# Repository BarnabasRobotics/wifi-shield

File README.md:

#Barnabas Robotics Wi-Fi shield
WIFI Shield for Barnabas-Bot and Arduino Uno
#First Schematic and basic board layout
We have added the first version of the barnabas bot Wi-Fi shield. This is version 1.0 with 4 DC motors max, and the NodeMCU Wi-Fi development board. There is no routing yet.  
#NodeMCU
Some information on NodeMCU 1.0 found here: https://github.com/nodemcu/nodemcu-devkit-v1.0
We have an EAGLE library for NodeMCU if you need to use it. This was developed by NodeMCU and it is also on their NodeMCU devkit v1.0 repository.  
#V2 
Some minor edits, added a GPIO header, and fixed some bad wires. Vincent will continue on the board layout.

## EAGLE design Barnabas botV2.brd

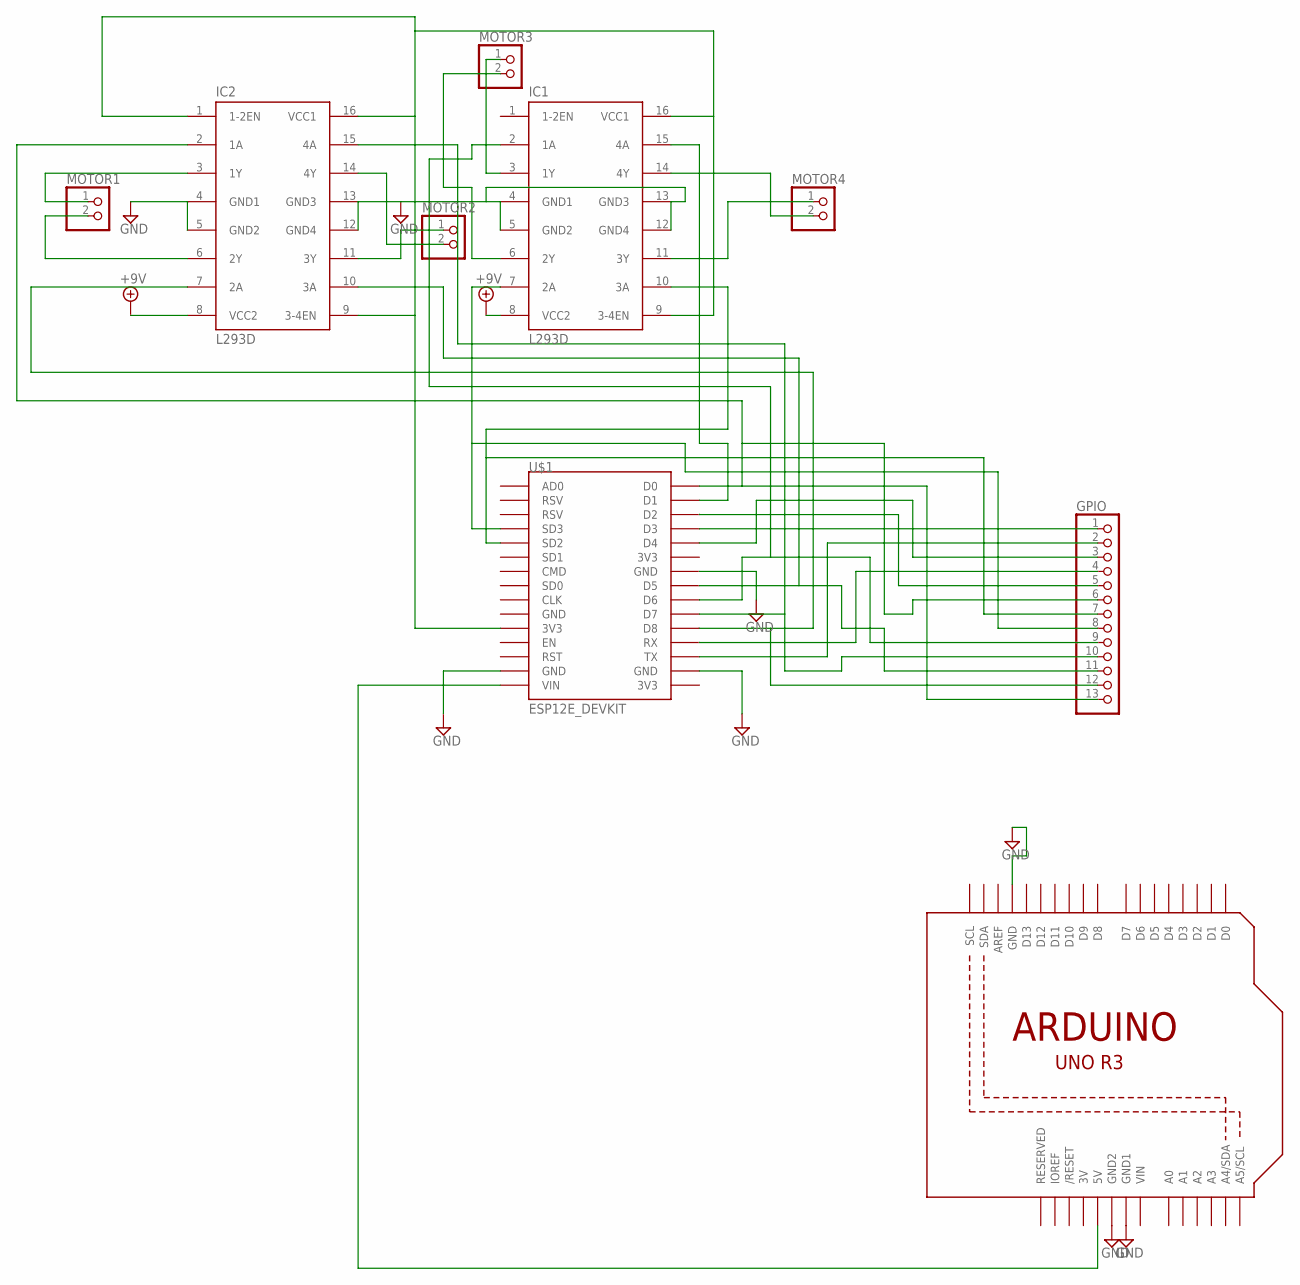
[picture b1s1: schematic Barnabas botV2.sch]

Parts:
GPIO: PINHD-1X13; 1X13
IC1, IC2: L293D; DIL16
MOTOR1, MOTOR2, MOTOR3, MOTOR4: PINHD-1X2; 1X02
U1: ARDUINOR3-DIMENSION; ARDUINOR3
U$1: ESP12E_DEVKIT

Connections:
3V: U1.3V
+9V: IC1.8 (VCC2), IC2.8 (VCC2)
GND: IC1.4 (GND1), IC1.5 (GND2), IC1.12 (GND4), IC1.13 (GND3), IC2.4 (GND1), IC2.5 (GND2), IC2.12 (GND4), IC2.13 (GND3), U1.GND, U1.GND1, U1.GND2, U$1.GND@1 (GND), U$1.GND@2 (GND), U$1.GND@3 (GND)
unnamed: GPIO.1, U$1.D3
unnamed: GPIO.12, IC2.7 (2A), U$1.D8
unnamed: IC1.9 (3-4EN), IC1.16 (VCC1), IC2.1 (1-2EN), IC2.9 (3-4EN), IC2.16 (VCC1), U$1.3V3@0 (3V3)
unnamed: GPIO.11, IC2.10 (3A), U$1.D5
unnamed: GPIO.10, IC2.15 (4A), U$1.D7
unnamed: GPIO.9, IC1.2 (1A), U$1.D6
unnamed: GPIO.8, IC1.7 (2A), U$1.SD3
unnamed: GPIO.7, IC1.10 (3A), U$1.SD2
unnamed: IC1.15 (4A), U$1.D1
unnamed: IC2.3 (1Y), MOTOR1.1
unnamed: IC2.6 (2Y), MOTOR1.2
unnamed: IC2.11 (3Y), MOTOR2.1
unnamed: IC2.14 (4Y), MOTOR2.2
unnamed: IC1.3 (1Y), MOTOR3.1
unnamed: IC1.14 (4Y), MOTOR4.2
unnamed: IC1.11 (3Y), MOTOR4.1
unnamed: GPIO.2, U$1.TX
unnamed: U1.5V, U$1.VIN
unnamed: GPIO.3, U$1.D4
unnamed: GPIO.4, U$1.RX
unnamed: GPIO.5, U$1.D2
unnamed: GPIO.6, GPIO.13, IC2.2 (1A), U$1.D0
VIN: U1.VIN

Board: 2 copper layers, 9 parts (0 on the bottom side), 24 nets, no tracks yet.

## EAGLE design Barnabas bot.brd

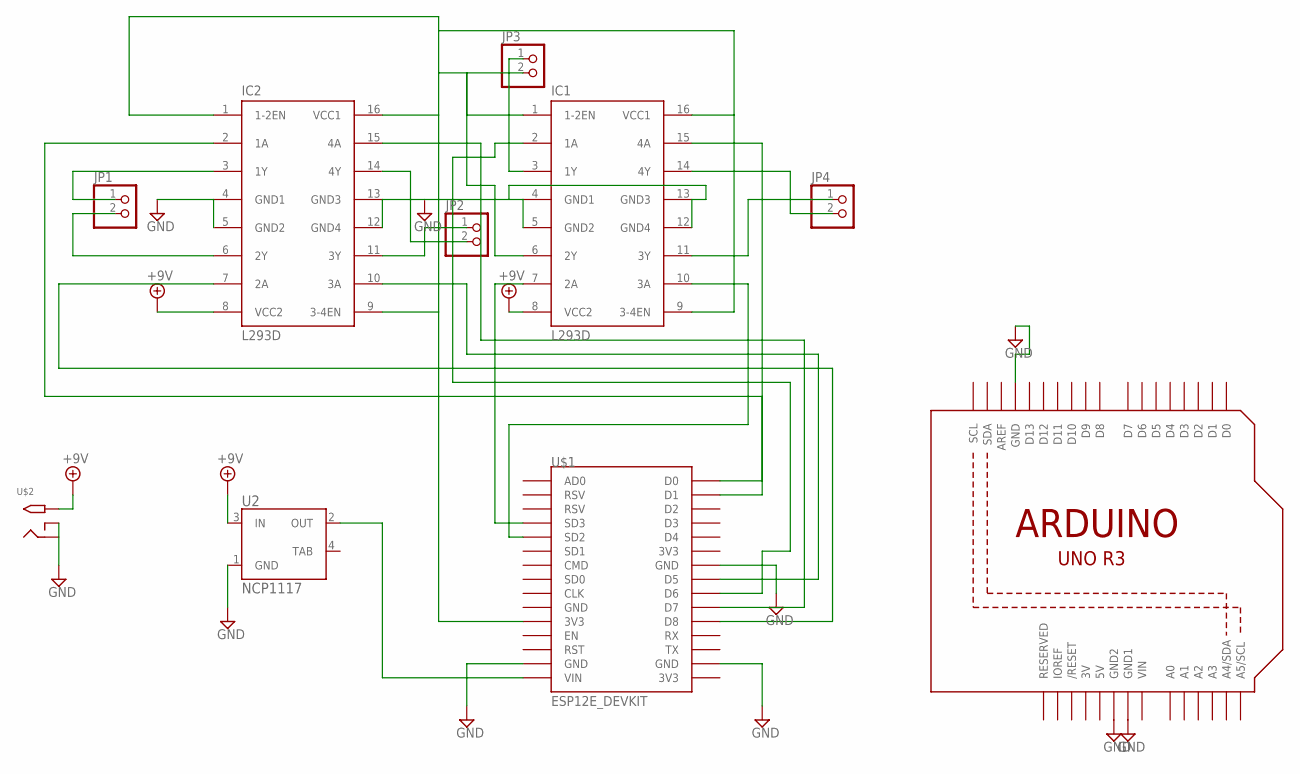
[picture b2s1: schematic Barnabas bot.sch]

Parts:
IC1, IC2: L293D; DIL16
JP1, JP2, JP3, JP4: PINHD-1X2; 1X02
U1: ARDUINOR3-DIMENSION; ARDUINOR3
U2: NCP1117; SOT223
U$1: ESP12E_DEVKIT
U$2: 2.1MMJACKTHM; PJ-102A

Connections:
3V: U1.3V
5V: U1.5V
+9V: IC1.8 (VCC2), IC2.8 (VCC2), U2.3 (IN), U$2.TIP
GND: IC1.4 (GND1), IC1.5 (GND2), IC1.12 (GND4), IC1.13 (GND3), IC2.4 (GND1), IC2.5 (GND2), IC2.12 (GND4), IC2.13 (GND3), U1.GND, U1.GND1, U1.GND2, U2.1 (GND), U$1.GND@1 (GND), U$1.GND@2 (GND), U$1.GND@3 (GND), U$2.RING_SW
unnamed: IC2.7 (2A), U$1.D8
unnamed: IC1.1 (1-2EN), IC1.9 (3-4EN), IC1.16 (VCC1), IC2.1 (1-2EN), IC2.9 (3-4EN), IC2.16 (VCC1), U$1.3V3@0 (3V3)
unnamed: IC2.2 (1A), U$1.D0
unnamed: IC2.10 (3A), U$1.D5
unnamed: IC2.15 (4A), U$1.D7
unnamed: IC1.2 (1A), U$1.D6
unnamed: IC1.7 (2A), U$1.SD3
unnamed: IC1.10 (3A), U$1.SD2
unnamed: IC1.15 (4A), U$1.D1
unnamed: IC2.3 (1Y), JP1.1
unnamed: IC2.6 (2Y), JP1.2
unnamed: IC2.11 (3Y), JP2.1
unnamed: IC2.14 (4Y), JP2.2
unnamed: IC1.3 (1Y), JP3.1
unnamed: IC1.6 (2Y), JP3.2
unnamed: IC1.14 (4Y), JP4.2
unnamed: IC1.11 (3Y), JP4.1
unnamed: U2.2 (OUT), U$1.VIN
VIN: U1.VIN

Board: 2 copper layers, 10 parts (0 on the bottom side), 20 nets, no tracks yet.

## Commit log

2016-07-13 Create license
2016-07-14 schematic and basic board layout
2016-07-14 Commit 1 comments
2016-07-14 An EAGLE library for the NodeMCU devkit 1.0
2016-07-14 Update!
2016-07-14 correction
2016-09-04 Editing to V2 of prototyping
    Made some minor edits, added things.
2016-09-04 V2 Update
    We explained the changes to V2 schematic.
2016-09-04 tiny update
    :D
